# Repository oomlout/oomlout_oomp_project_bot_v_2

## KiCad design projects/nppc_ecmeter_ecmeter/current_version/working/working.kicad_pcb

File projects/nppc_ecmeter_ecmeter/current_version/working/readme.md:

# ecmeter
 
## summary 
* id: nppc_ecmeter_ecmeter
* user: nppc
* name: ecmeter
* board: ecmeter
* repo: https://github.com/nppc/ECmeter
* src_file_repo_kicad_pcb: KiCad/ECmeter.kicad_pcb
* src_file_repo_kicad_pcb_link: https://github.com/nppc/ECmeter/tree/main/KiCad/ECmeter.kicad_pcb

* src_file_repo_sch: KiCad/ECmeter.sch
* src_file_repo_sch_link: https://github.com/nppc/ECmeter/tree/main/KiCad/ECmeter.sch
* full details link: https://github.com/oomlout/oomlout_oomp_project_bot_v_2/tree/main/projects/nppc_ecmeter_ecmeter/current_version/working

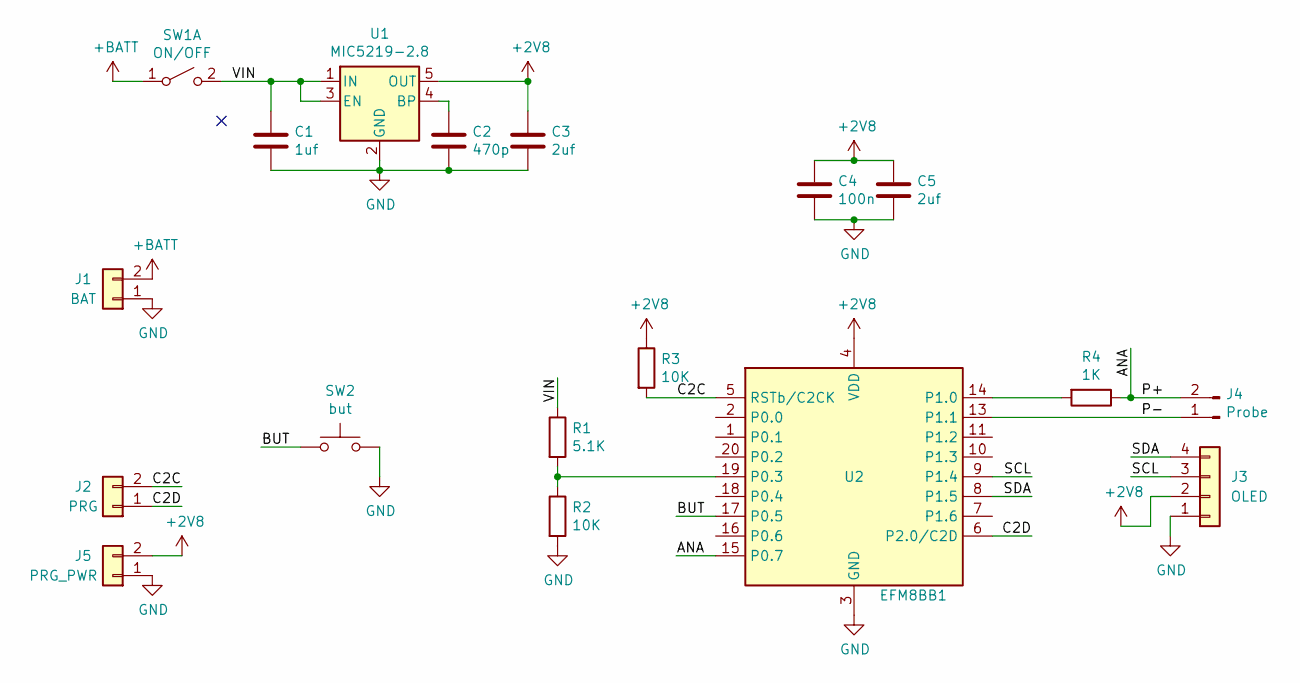
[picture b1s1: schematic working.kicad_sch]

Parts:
C1: 1uf; C_0603
C2: 470p; C_0603
C3, C5: 2uf; C_0603
C4: 100n; C_0603
J1: BAT; Conn_1x02_2.54_0.9mm
J2: PRG; POWER2PIN_2
J3: OLED; Pin_Header_Straight_1x04_Pitch2.54mm
J4: Probe; POWER2PIN_2
J5: PRG_PWR; POWER2PIN_2
R1: 5.1K; R_0603
R2, R3: 10K; R_0603
R4: 1K; R_0603
SW1: ON/OFF; Conn_1x02_2.54_0.9mm
SW2: but; POWER2PIN_2
U1: MIC5219-2.8; SOT-23-5
U2: EFM8BB1; QFN20

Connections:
+2V8: C3.1, C4.1, C5.1, J3.2, J5.2, R3.1, U1.5 (OUT), U2.4 (VDD)
+BATT: J1.2, SW1.1 (A)
/ANA: J4.2, R4.1, U2.15 (P0.7)
/BUT: SW2.1, U2.17 (P0.5)
/C2C: J2.2, R3.2, U2.5 (RSTb/C2CK)
/C2D: J2.1, U2.6 (P2.0/C2D)
/P-: J4.1, U2.13 (P1.1)
/SCL: J3.3, U2.9 (P1.4)
/SDA: J3.4, U2.8 (P1.5)
/VIN: C1.1, R1.1, SW1.2 (B), U1.1 (IN), U1.3 (EN)
GND: C1.2, C2.2, C3.2, C4.2, C5.2, J1.1, J3.1, J5.1, R2.2, SW2.2, U1.2 (GND), U2.3 (GND), U2.12 (GND), U2.21 (GND)
unnamed: C2.1, U1.4 (BP)
unnamed: R1.2, R2.1, U2.19 (P0.3)
unnamed: R4.2, U2.14 (P1.0)

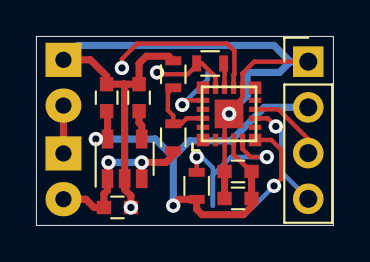
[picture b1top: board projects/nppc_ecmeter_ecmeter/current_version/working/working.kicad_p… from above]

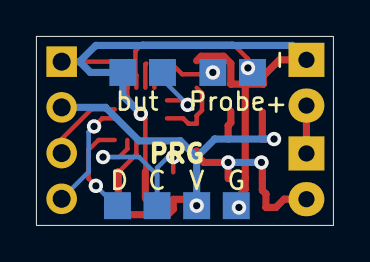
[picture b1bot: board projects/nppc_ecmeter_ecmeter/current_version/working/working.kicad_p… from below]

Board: 2 copper layers, 16.5 x 10.5 mm, 18 parts (4 on the bottom side), 14 nets.

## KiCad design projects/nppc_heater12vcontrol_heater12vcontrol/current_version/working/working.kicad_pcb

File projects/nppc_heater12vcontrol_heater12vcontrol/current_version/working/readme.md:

# heater12vcontrol
 
## summary 
* id: nppc_heater12vcontrol_heater12vcontrol
* user: nppc
* name: heater12vcontrol
* board: heater12vcontrol
* repo: https://github.com/nppc/Heater12VControl
* src_file_repo_kicad_pcb: KiCad/Heater12VControl.kicad_pcb
* src_file_repo_kicad_pcb_link: https://github.com/nppc/Heater12VControl/tree/master/KiCad/Heater12VControl.kicad_pcb

* src_file_repo_sch: KiCad/Heater12VControl.sch
* src_file_repo_sch_link: https://github.com/nppc/Heater12VControl/tree/master/KiCad/Heater12VControl.sch
* full details link: https://github.com/oomlout/oomlout_oomp_project_bot_v_2/tree/main/projects/nppc_heater12vcontrol_heater12vcontrol/current_version/working

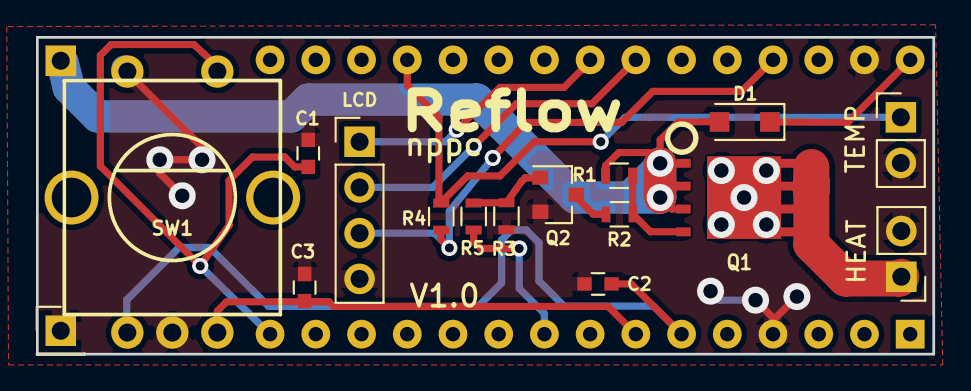
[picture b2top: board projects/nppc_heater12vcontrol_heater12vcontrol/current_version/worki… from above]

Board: 2 copper layers, 49.8 x 17.6 mm, 18 parts (1 on the bottom side), 15 nets.

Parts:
12V: PWR; Pin_Header_Straight_1x01_Pitch2.54mm
C1, C2, C3: 22n; C_0603
D1: D; D_SOD-123F
GND: PWR; Pin_Header_Straight_1x01_Pitch2.54mm
HEAT: Heater; Pin_Header_Straight_1x02_Pitch2.54mm
J4: Arduino_Nano_Header; Arduino_Nano
LCD: LCD; Pin_Header_Straight_1x04_Pitch2.54mm
Q1: AON6403; DFN-8-1EP_6x5mm
Q2: SI2308; SOT-23
R1: 100K; R_0603
R2: 1K; R_0603
R3: 10K; R_0603
R4: 4.7K; R_0603
R5: 100; R_0603
SW1: Rotary_Encoder; ROTARY-ENCODER
TEMP: Temp sensor; Pin_Header_Straight_1x02_Pitch2.54mm

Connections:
+12V: 12V.1, D1.2, Q1.3, R1.1
/Heat: J4.9, R5.1
/Temp: J4.19, R4.1, TEMP.1
GND: C1.2, C2.2, C3.2, GND.1, HEAT.2, J4.4, J4.29, LCD.4, Q2.2, R3.2, SW1.2, SW1.4, TEMP.2
unnamed: C1.1, J4.15, SW1.5
unnamed: C2.1, J4.6, SW1.1
unnamed: C3.1, J4.7, SW1.3
unnamed: D1.1, J4.30
unnamed: HEAT.1, Q1.2
unnamed: J4.23, LCD.1
unnamed: J4.24, LCD.2
unnamed: Q1.1, R1.2, R2.1
unnamed: Q2.1, R3.1, R5.2
unnamed: Q2.3, R2.2
VCC: J4.27, LCD.3, R4.2

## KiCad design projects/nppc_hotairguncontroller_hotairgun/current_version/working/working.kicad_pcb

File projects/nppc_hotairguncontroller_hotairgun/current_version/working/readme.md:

# hotairguncontroller
 
## summary 
* id: nppc_hotairguncontroller_hotairgun
* user: nppc
* name: hotairguncontroller
* board: hotairgun
* repo: https://github.com/nppc/HotAirGunController
* src_file_repo_kicad_pcb: KiCad/HotAirGun.kicad_pcb
* src_file_repo_kicad_pcb_link: https://github.com/nppc/HotAirGunController/tree/master/KiCad/HotAirGun.kicad_pcb

* src_file_repo_sch: KiCad/HotAirGun.sch
* src_file_repo_sch_link: https://github.com/nppc/HotAirGunController/tree/master/KiCad/HotAirGun.sch
* full details link: https://github.com/oomlout/oomlout_oomp_project_bot_v_2/tree/main/projects/nppc_hotairguncontroller_hotairgun/current_version/working

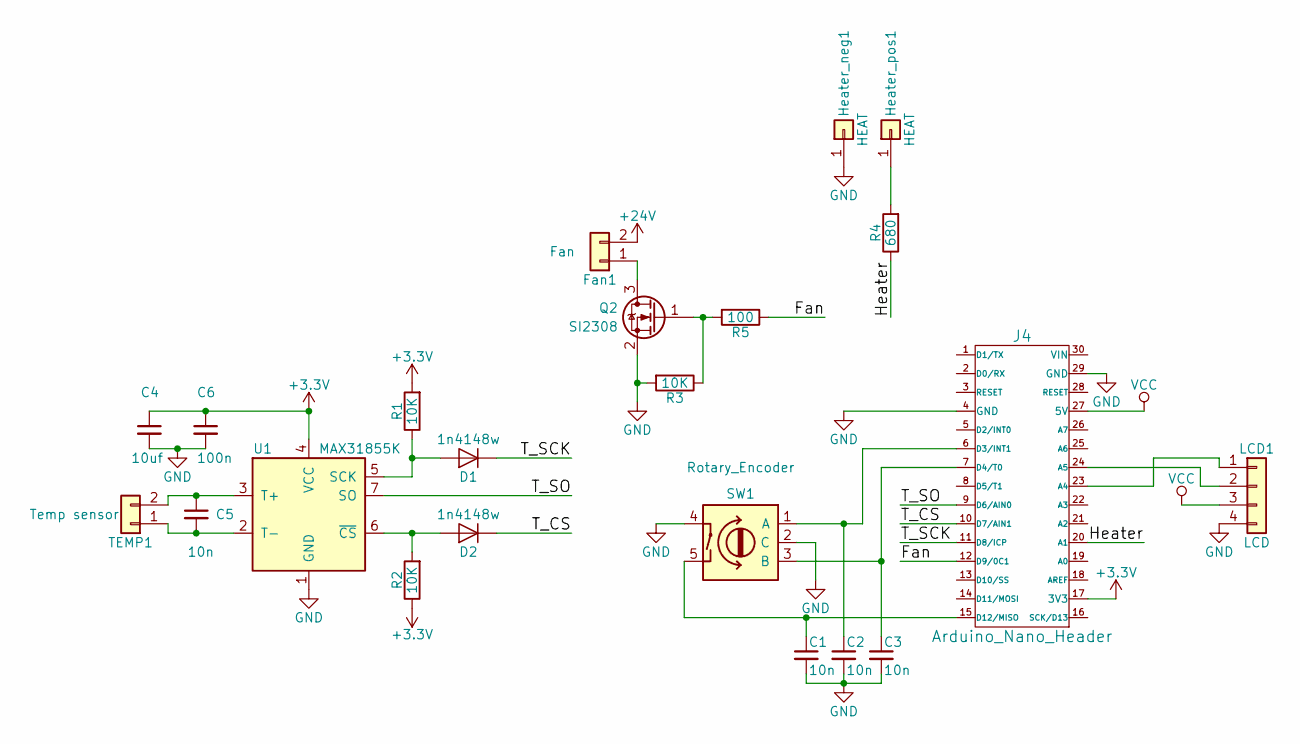
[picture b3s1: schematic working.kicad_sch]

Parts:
C1, C2, C3, C5: 10n; C_0603
C4: 10uf; C_0603
C6: 100n; C_0603
D1, D2: 1n4148w; D_SOD-523
Fan1: Fan; Pin_Header_Straight_1x02_Pitch2.54mm
Heater_neg1: HEAT; Pin_Header_Angled_1x01_Pitch2.54mm
Heater_pos1: HEAT; Pin_Header_Angled_1x01_Pitch2.54mm
J4: Arduino_Nano_Header; Arduino_Nano
LCD1: LCD; Pin_Header_Straight_1x04_Pitch2.54mm
Q2: SI2308; SOT-23
R1, R2, R3: 10K; R_0603
R4: 680; R_0603
R5: 100; R_0603
SW1: Rotary_Encoder; SF-ROTARY-ENCODER
TEMP1: Temp sensor; Pin_Header_Straight_1x02_Pitch2.54mm
U1: MAX31855K; SOIC-8_3.9x4.9mm_Pitch1.27mm

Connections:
+3V3: C4.1, C6.1, J4.17 (3V3), R1.2, R2.1, U1.4 (VCC)
/Fan: J4.12 (D9/0C1), R5.1
/Heater: J4.20 (A1), R4.1
/T_CS: D2.1 (K), J4.10 (D7/AIN1)
/T_SCK: D1.1 (K), J4.11 (D8/ICP)
/T_SO: J4.9 (D6/AIN0), U1.7 (SO)
GND: C1.2, C2.2, C3.2, C4.2, C6.2, Heater_neg1.1, J4.4 (GND), J4.29 (GND), LCD1.4, Q2.2 (S), R3.2, SW1.2 (C), SW1.4, U1.1 (GND)
unnamed: C1.1, J4.15 (D12/MISO), SW1.5
unnamed: C2.1, J4.6 (D3/INT1), SW1.1 (A)
unnamed: C3.1, J4.7 (D4/T0), SW1.3 (B)
unnamed: C5.1, TEMP1.2, U1.3 (T+)
unnamed: C5.2, TEMP1.1, U1.2 (T-)
unnamed: D1.2 (A), R1.1, U1.5 (SCK)
unnamed: D2.2 (A), R2.2, U1.6 (~CS)
unnamed: Fan1.1, Q2.3 (D)
unnamed: Heater_pos1.1, R4.2
unnamed: J4.23 (A4), LCD1.1
unnamed: J4.24 (A5), LCD1.2
unnamed: Q2.1 (G), R3.1, R5.2
VCC: J4.27 (5V), LCD1.3

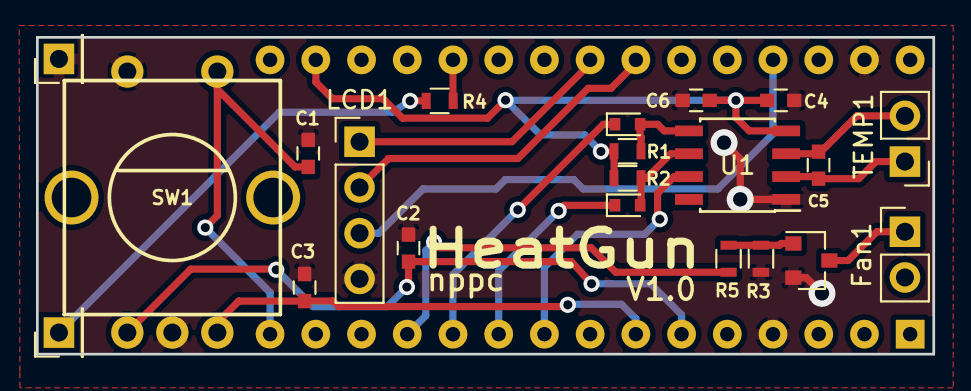
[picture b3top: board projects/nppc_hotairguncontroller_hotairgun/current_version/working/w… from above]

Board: 2 copper layers, 49.8 x 17.6 mm, 22 parts (1 on the bottom side), 20 nets.

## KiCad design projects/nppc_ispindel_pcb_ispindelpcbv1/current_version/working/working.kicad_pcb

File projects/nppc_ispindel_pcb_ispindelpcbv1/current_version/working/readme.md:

# ispindel_pcb
 
## summary 
* id: nppc_ispindel_pcb_ispindelpcbv1
* user: nppc
* name: ispindel_pcb
* board: ispindelpcbv1
* repo: https://github.com/nppc/iSpindel-PCB
* src_file_repo_kicad_pcb: KiCad/iSpindel-shields/iSpindelPCBv1.kicad_pcb
* src_file_repo_kicad_pcb_link: https://github.com/nppc/iSpindel-PCB/tree/master/KiCad/iSpindel-shields/iSpindelPCBv1.kicad_pcb

* src_file_repo_sch: KiCad/iSpindel-shields/iSpindelPCBv1.sch
* src_file_repo_sch_link: https://github.com/nppc/iSpindel-PCB/tree/master/KiCad/iSpindel-shields/iSpindelPCBv1.sch
* full details link: https://github.com/oomlout/oomlout_oomp_project_bot_v_2/tree/main/projects/nppc_ispindel_pcb_ispindelpcbv1/current_version/working

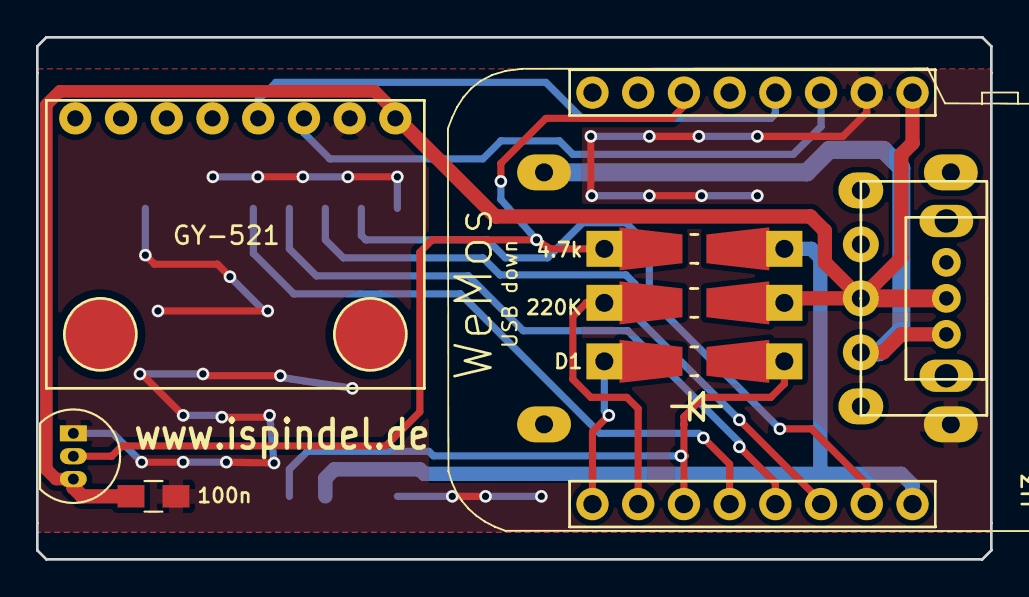
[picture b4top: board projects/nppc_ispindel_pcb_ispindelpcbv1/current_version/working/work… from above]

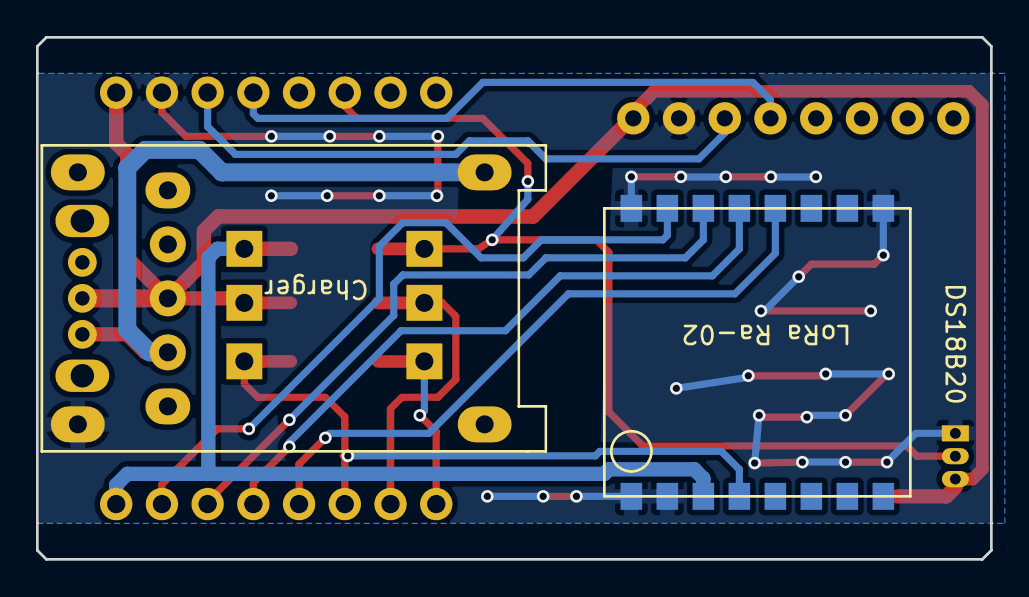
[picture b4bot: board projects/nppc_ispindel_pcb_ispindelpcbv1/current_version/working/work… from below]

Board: 2 copper layers, 53.0 x 29.0 mm, 11 parts (2 on the bottom side), 14 nets.

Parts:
C1: 100n; C_0805_HandSoldering
D1: Schottky; Resistor_SMD+THTuniversal_0805to1206_RM10_HandSoldering
R1: 220K; Resistor_SMD+THTuniversal_0805to1206_RM10_HandSoldering
R2: 4.7k; Resistor_SMD+THTuniversal_0805to1206_RM10_HandSoldering
SW1: SW_SPDT; SK12D07VG3
SW2: SW_SPDT; SS-12F23
U1: GY-521
U2: LoRa_Ra-02
U3: WeMos_mini; wemos_D1_mini_board
U4: TP4056-shield-6PIN
U5: DS18B20; TO-92_Inline_Narrow_Oval

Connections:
+3V3: R2.1, U2.3, U3.16
+5V: C1.1, R1.2, SW1.2, SW2.2, U1.1, U3.1, U5.3
/MISO: U2.13, U3.13
/MOSI: U2.14, U3.14
/NSS: U2.15, U3.15
/RES: D1.1, U2.4, U3.11
/SCK: U2.12, U3.12
/SCL: U1.3, U3.3
/SDA: U1.4, U3.4
/Temp: R2.2, U3.6, U5.2
GND: C1.2, U1.2, U2.1, U2.2, U2.9, U2.16, U3.2, U4.2, U5.1
unnamed: D1.2, U3.9
unnamed: R1.1, U3.10
unnamed: SW1.1, SW2.1, U4.3

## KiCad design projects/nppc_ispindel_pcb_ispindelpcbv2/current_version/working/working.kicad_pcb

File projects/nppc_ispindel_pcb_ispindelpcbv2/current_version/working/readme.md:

# ispindel_pcb
 
## summary 
* id: nppc_ispindel_pcb_ispindelpcbv2
* user: nppc
* name: ispindel_pcb
* board: ispindelpcbv2
* repo: https://github.com/nppc/iSpindel-PCB
* src_file_repo_kicad_pcb: KiCad/iSpindel-smd/iSpindelPCBv2.kicad_pcb
* src_file_repo_kicad_pcb_link: https://github.com/nppc/iSpindel-PCB/tree/master/KiCad/iSpindel-smd/iSpindelPCBv2.kicad_pcb

* src_file_repo_sch: KiCad/iSpindel-smd/iSpindelPCBv2.sch
* src_file_repo_sch_link: https://github.com/nppc/iSpindel-PCB/tree/master/KiCad/iSpindel-smd/iSpindelPCBv2.sch
* full details link: https://github.com/oomlout/oomlout_oomp_project_bot_v_2/tree/main/projects/nppc_ispindel_pcb_ispindelpcbv2/current_version/working

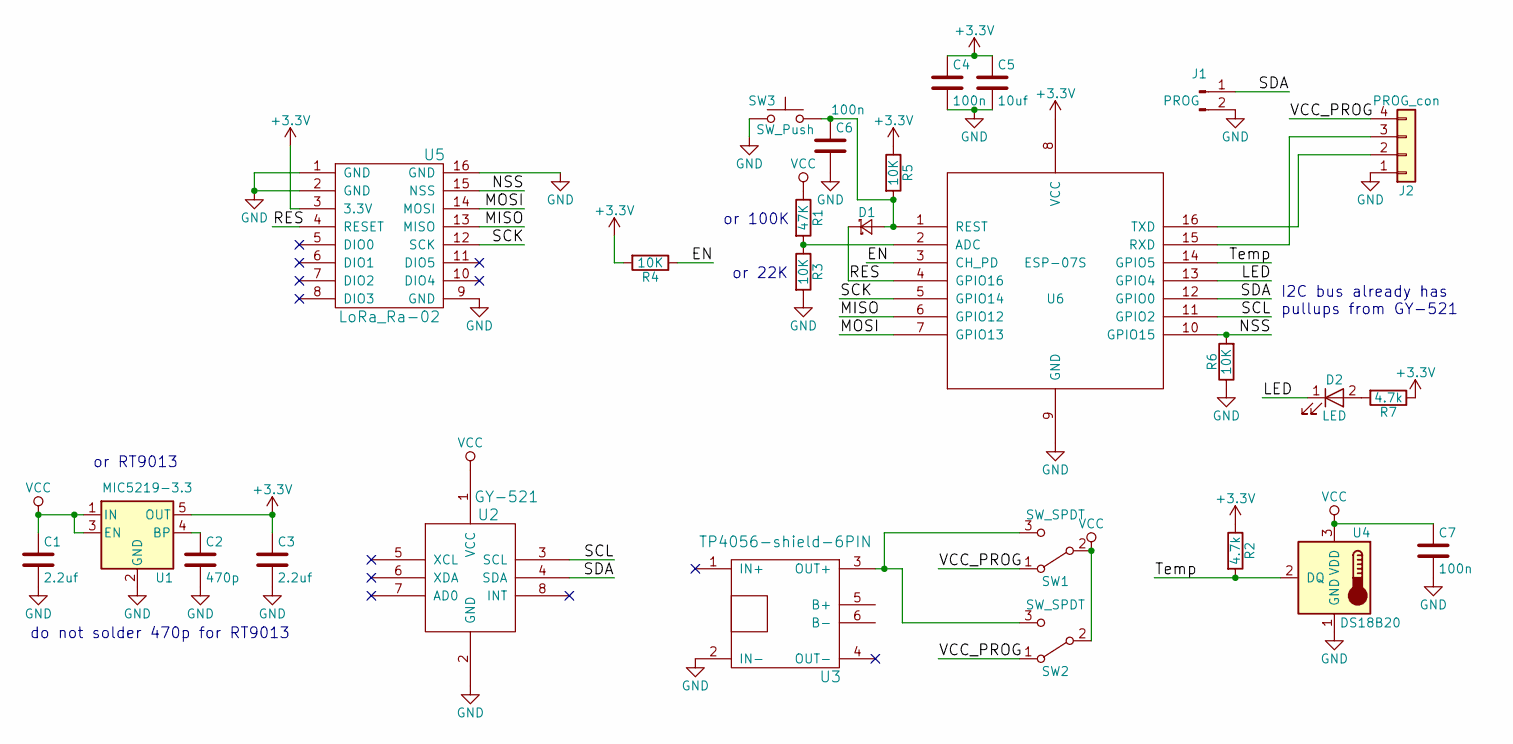
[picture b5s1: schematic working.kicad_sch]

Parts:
C1, C3: 2.2uf; C_0805
C2: 470p; C_0603
C4, C6, C7: 100n; C_0603
C5: 10uf; C_0805
D1: Schottky; D_SOD-323
D2: LED; LED_0805
J1: PROG; Pin_Header_Straight_1x02_Pitch2.54mm
J2: PROG_con; Pin_Header_Straight_1x04_Pitch2.54mm
R1: 47K; R_0603
R2, R7: 4.7k; R_0603
R3, R4, R5, R6: 10K; R_0603
SW1: SW_SPDT; SK12D07VG3
SW2: SW_SPDT; SS-12F23
SW3: SW_Push; Button_TS-018
U1: MIC5219-3.3; SOT-23-5
U2: GY-521
U3: TP4056-shield-6PIN
U4: DS18B20; TO-92_Inline_Narrow_Oval
U5: LoRa_Ra-02
U6: ESP-07S

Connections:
+3V3: C3.1, C4.1, C5.1, R2.1, R4.2, R5.1, R7.1, U1.5 (OUT), U5.3 (3.3V), U6.8 (VCC)
/EN: R4.1, U6.3 (CH_PD)
/LED: D2.1 (K), U6.13 (GPIO4)
/MISO: U5.13 (MISO), U6.6 (GPIO12)
/MOSI: U5.14 (MOSI), U6.7 (GPIO13)
/NSS: R6.2, U5.15 (NSS), U6.10 (GPIO15)
/RES: D1.1 (K), U5.4 (RESET), U6.4 (GPIO16)
/SCK: U5.12 (SCK), U6.5 (GPIO14)
/SCL: U2.3 (SCL), U6.11 (GPIO2)
/SDA: J1.1, U2.4 (SDA), U6.12 (GPIO0)
/Temp: R2.2, U4.2 (DQ), U6.14 (GPIO5)
/VCC_PROG: J2.4, SW1.1 (A), SW2.1 (A)
GND: C1.2, C2.2, C3.2, C4.2, C5.2, C6.2, C7.2, J1.2, J2.1, R3.2, R6.1, SW3.2, U1.2 (GND), U2.2 (GND), U3.2 (IN-), U4.1 (GND), U5.1 (GND), U5.2 (GND), U5.9 (GND), U5.16 (GND), U6.9 (GND)
unnamed: C2.1, U1.4 (BP)
unnamed: C6.1, D1.2 (A), R5.2, SW3.1, U6.1 (REST)
unnamed: D2.2 (A), R7.2
unnamed: J2.2, U6.16 (TXD)
unnamed: J2.3, U6.15 (RXD)
unnamed: R1.2, R3.1, U6.2 (ADC)
unnamed: SW1.3 (C), SW2.3 (C), U3.3 (OUT+)
VCC: C1.1, C7.1, R1.1, SW1.2 (B), SW2.2 (B), U1.1 (IN), U1.3 (EN), U2.1 (VCC), U4.3 (VDD)

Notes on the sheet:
or 100K
I2C bus already has pullups from GY-521
do not solder 470p for RT9013
or 22K
or RT9013

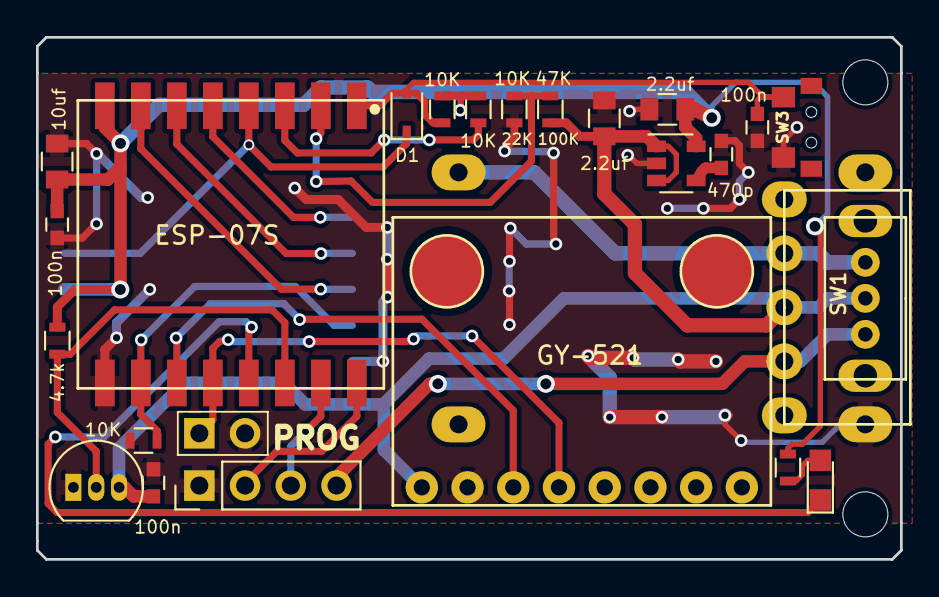
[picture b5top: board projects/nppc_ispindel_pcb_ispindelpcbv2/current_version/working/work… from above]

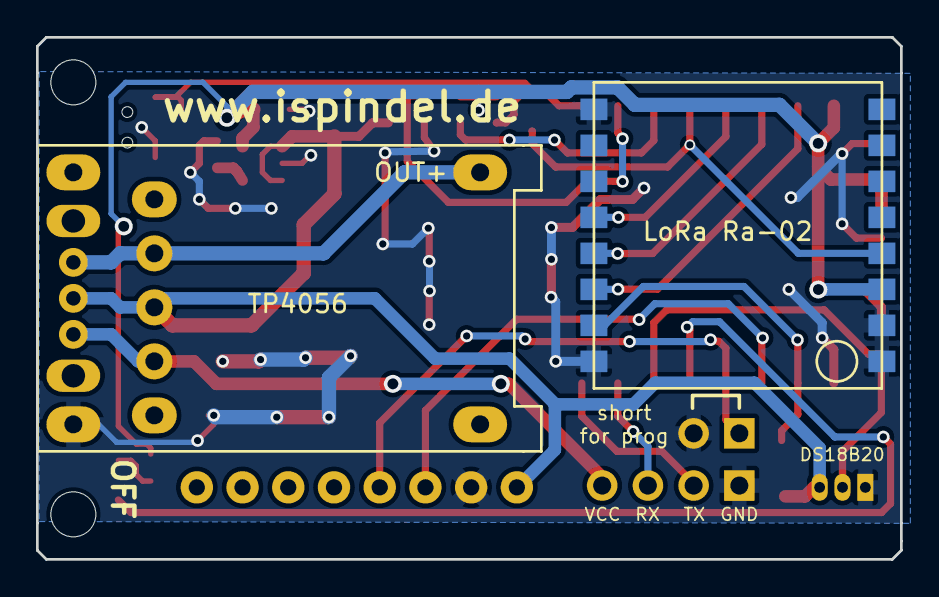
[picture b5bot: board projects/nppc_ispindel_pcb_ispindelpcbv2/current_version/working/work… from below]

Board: 2 copper layers, 48.0 x 29.0 mm, 27 parts (2 on the bottom side), 21 nets.

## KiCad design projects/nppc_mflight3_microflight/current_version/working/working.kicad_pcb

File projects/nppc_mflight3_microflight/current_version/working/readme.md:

# mflight3
 
## summary 
* id: nppc_mflight3_microflight
* user: nppc
* name: mflight3
* board: microflight
* repo: https://github.com/nppc/Mflight3
* src_file_repo_kicad_pcb: KiCad/MicroFlight/MicroFlight.kicad_pcb
* src_file_repo_kicad_pcb_link: https://github.com/nppc/Mflight3/tree/master/KiCad/MicroFlight/MicroFlight.kicad_pcb

* src_file_repo_sch: 
* src_file_repo_sch_link: https://github.com/nppc/Mflight3/tree/master/
* full details link: https://github.com/oomlout/oomlout_oomp_project_bot_v_2/tree/main/projects/nppc_mflight3_microflight/current_version/working

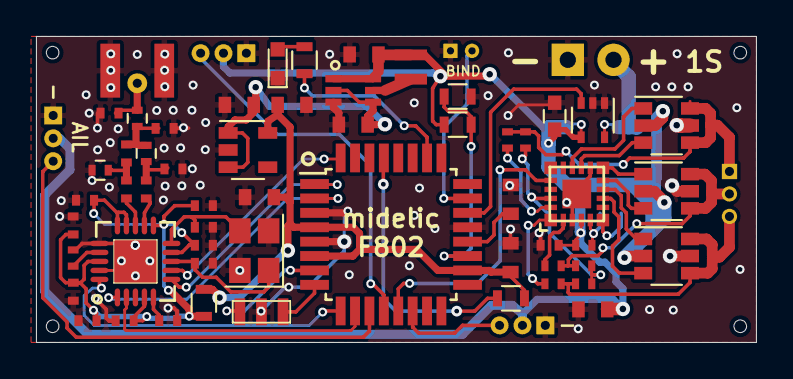
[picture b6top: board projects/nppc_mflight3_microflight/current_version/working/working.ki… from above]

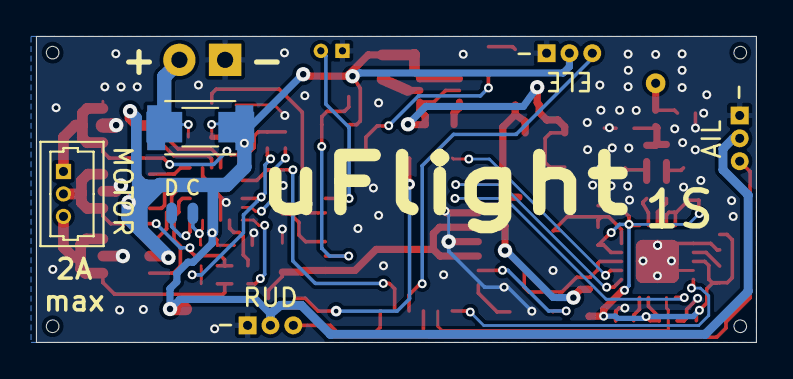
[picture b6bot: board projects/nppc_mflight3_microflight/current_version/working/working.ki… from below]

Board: 2 copper layers, 40.0 x 17.0 mm, 66 parts (8 on the bottom side), 50 nets.

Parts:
AE1: ANT; ANT_PCB
C1, C3, C25: 10uf; C_0603
C2: 10n; C_0603
C4: 100n; C_0603
C5, C6, C7: 2uf; C_0603
C8, C10, C16, C17, C26: 100n; C_0402
C9: 2uf; C_0402
C11, C14: 27p; C_0402
C12, C13, C15: 220p; C_0402
C18, C19: 100p; C_0402
C20, C21: 1p; C_0402
C22, C23: 1.8p; C_0402
C24: 47uf; C_0603
D1: LED; LED_0603
J1: C2CK; PAD_1.2X0.6_Round
J2: C2D; PAD_1.2X0.6_Round
J3: MOTOR; Molex_PicoBlade_53047-0310_03x1.25mm_Straight
J6: BIND; Conn2pin_small
J7: BAT; Conn_1x02_2.54mm
J8: SRV1; Pin_Header_Straight_1x03_Pitch1.27mm
J9: SRV2; Pin_Header_Straight_1x03_Pitch1.27mm
J10: SRV3; Pin_Header_Straight_1x03_Pitch1.27mm
L1: 4.7uH; InductorXFL2006
L2: 1000; L_0603
L3, L4, L5: 1.2n; L_0402
Q1, Q2, Q3: DUAL_NP; SuperSOT-6
R1, R4: 10K; R_0603
R2: 18K; R_0603
R3: 1K; R_0603
R5: 56K; R_0402_NoSilk
R6, R7, R9, R11: 1K; R_0402_NoSilk
R8, R10, R12: 10K; R_0402_NoSilk
R13: 0.022; R_1206_HandSoldering
R14: 0.022; R_2010
U1: TPS61222; SC-70-6
U2: ATmega328P-AU; TQFP-32_7x7mm_Pitch0.8mm
U3: RT9013-33; SOT-23-5
U4: CC2500
U5: EFM8BB21; QFN20
U6: MAX9610; SOT-353_SC-70-5
Y1: 16MHZ; Ceramic_Resonator_SMD_3mm
Y2: 26MHZ; Crystal_SMD_SeikoEpson_FA238-4pin_3.2x2.5mm

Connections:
+3V3: C4.1, C6.1, C7.1, L2.1, R4.1, U2.4, U2.6, U2.18, U3.5
+BATT: C1.1, C24.2, C25.2, C26.2, J8.2, J9.2, J10.2, L1.1, Q1.2, Q2.2, Q3.2, R1.2, R6.1, R13.1, R14.1, U1.1, U1.6, U5.4, U6.4
/5V: C3.1, C5.1, U1.2, U1.4, U3.1, U3.3
/A1: R1.1, R2.2, U2.19
/A2: U2.22, U6.3
/CH1: J8.3, U2.11
/CH2: J9.3, U2.12
/CH3: U2.13, U5.17
/CH4: J10.3, U2.14
/CSN: U2.32, U4.7
/GDO0: U2.1, U4.6
/SCLK: U2.2, U4.1
/SI: U2.9, U4.20
/SO: U2.10, U4.2
/uESC1S/Ac: Q1.3, U5.13
/uESC1S/Ap: Q1.1, U5.14
/uESC1S/Bc: Q2.3, U5.10
/uESC1S/Bp: Q2.1, U5.11
/uESC1S/Cc: Q3.3, U5.8
/uESC1S/Cp: Q3.1, U5.9
/uESC1S/M_A: J3.1, Q1.4, Q1.6, R7.2, R8.1
/uESC1S/M_B: J3.2, Q2.4, Q2.6, R9.2, R10.1
/uESC1S/M_C: J3.3, Q3.4, Q3.6, R11.2, R12.1
GND: AE1.2, C1.2, C2.2, C3.2, C4.2, C5.2, C6.2, C7.2, C8.1, C9.2, C10.1, C11.1, C12.2, C13.1, C14.1, C15.2, C16.1, C17.1, C20.1, C22.1, C23.1, C24.1, C25.1, C26.1, D1.1, J6.1, J7.1, J8.1, J9.1, J10.1, L3.2, Q1.5, Q2.5, Q3.5, R2.1, R5.1, U1.3, U2.3, U2.5, U2.21, U3.2, U4.16, U4.19, U5.3, U5.12, U5.21, U6.1, U6.2, Y1.2, Y2.2, Y2.4
unnamed: AE1.1, C23.2, L5.2
unnamed: C2.1, U2.20
unnamed: C10.2, U4.5
unnamed: C11.2, U4.8, Y2.1
unnamed: C14.2, U4.10, Y2.3
unnamed: C18.1, C21.2, L3.1
unnamed: C18.2, U4.13
unnamed: C19.1, C20.2, L4.1
unnamed: C19.2, U4.12
unnamed: C21.1, C22.2, L4.2, L5.1
unnamed: D1.2, R3.1
unnamed: J1.1, R6.2, U5.5
unnamed: J2.1, U5.6
unnamed: J6.2, U2.23
unnamed: J7.2, R13.2, R14.2, U6.5
unnamed: L1.2, U1.5
unnamed: R3.2, U2.26
unnamed: R4.2, U2.29
unnamed: R5.2, U4.17
unnamed: R8.2, U5.20
unnamed: R10.2, U5.2
unnamed: R7.1, R9.1, R11.1, U5.19
unnamed: R12.2, U5.1
unnamed: U2.7, Y1.3
unnamed: U2.8, Y1.1
VCC: C8.2, C9.1, C12.1, C13.2, C15.1, C16.2, C17.2, L2.2, U4.4, U4.9, U4.11, U4.14, U4.15, U4.18
